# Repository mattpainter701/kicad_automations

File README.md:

<p align="center">

</p>

<p align="center">
  <strong>Programmatic KiCad schematic generation, strict validation, and manufacturing export<br>
  designed for AI-assisted hardware workflows — Claude Code, Codex, and offline CLI.</strong>
</p>

---

## How It Works

Every path through Circuit Weaver follows the same contract: **describe the design → validate → generate KiCad artifacts**. The diagram above shows what each module does and which function it calls. Pick your entry point (Claude Code skill, Codex agent, or CLI wizard) and the rest is automatic.

---

<!-- capability-registry:start -->
## Capability Contract

This table is generated from the checked-in capability registry. Regenerate it with `python scripts/gen_capability_docs.py`; do not edit it by hand.

Verification is conservative: a capability only claims the evidence level its public path actually verifies. **not applicable** means an operational capability makes no design-artifact verification claim; it is not a lower verification level.

| CLI capability | Maturity | Public surfaces | Verification contract | Evidence | Since |
|---|---|---|---|---|---|
| `validate` | beta | CLI: `validate`; Python: `circuit_weaver.dispatcher:validate_design`; HTTP: `POST /validate; POST /mvp/validate`; MCP: `validate_design`; Skill: `circuit-weaver` | `static-parse` → `static-parse` | `command-contract`, `static-parse` | 0.32.1 |
| `apply-patch` | beta | CLI: `apply-patch`; Python: `circuit_weaver.dispatcher:apply_design_patch`; HTTP: `POST /mvp/apply-patch` | `static-parse` → `static-parse` | `command-contract`, `static-parse` | 0.32.1 |
| `generate` | experimental | CLI: `generate`; Python: `circuit_weaver.dispatcher:generate_artifacts`; HTTP: `POST /generate; POST /mvp/generate`; MCP: `generate_artifacts`; Skill: `circuit-weaver` | `static-parse` → `static-parse` | `command-contract`, `static-parse`, `kicad-load`, `erc` | 0.32.1 |
| `review-report` | experimental | CLI: `review-report`; Skill: `circuit-weaver` | `static-parse` → `static-parse` | `command-contract`, `static-parse` | 0.32.1 |
| `diff` | beta | CLI: `diff`; Python: `circuit_weaver.dispatcher:diff_designs`; HTTP: `POST /mvp/diff` | `static-parse` → `static-parse` | `command-contract`, `static-parse` | 0.32.1 |
| `ingest-pcb-feedback` | beta | CLI: `ingest-pcb-feedback`; Python: `circuit_weaver.dispatcher:ingest_pcb_feedback`; HTTP: `POST /mvp/pcb-feedback` | `static-parse` → `static-parse` | `command-contract`, `static-parse` | 0.32.1 |
| `import-placement` | review_only | CLI: `import-placement`; Skill: `circuit-weaver` | `static-parse` → `static-parse` | `command-contract`, `static-parse` | 0.32.1 |
| `list-templates` | beta | CLI: `list-templates`; HTTP: `GET /templates` | not applicable (operational) | `command-contract` | 0.32.1 |
| `scaffold` | beta | CLI: `scaffold`; Skill: `circuit-weaver` | `static-parse` → `static-parse` | `command-contract`, `static-parse` | 0.32.1 |
| `register-ic` | experimental | CLI: `register-ic` | `static-parse` → `static-parse` | `command-contract`, `static-parse` | 0.32.1 |
| `resolve-symbol` | experimental | CLI: `resolve-symbol` | not applicable (operational) | `command-contract` | 0.33.0 |
| `export-jlcpcb` | review_only | CLI: `export-jlcpcb`; Skill: `circuit-weaver` | `static-parse` → `static-parse` | `command-contract`, `static-parse` | 0.32.1 |
| `export-gerbers` | review_only | CLI: `export-gerbers`; Skill: `circuit-weaver` | `static-parse` → `static-parse` | `command-contract`, `static-parse` | 0.32.1 |
| `cost-bom` | experimental | CLI: `cost-bom`; Skill: `circuit-weaver` | `static-parse` → `static-parse` | `command-contract`, `static-parse` | 0.32.1 |
| `import-design` | experimental | CLI: `import-design`; Python: `circuit_weaver.design_import:import_design`; Skill: `circuit-weaver` | `static-parse` → `static-parse` | `command-contract`, `static-parse` | 0.32.1 |
| `analyze-design` | experimental | CLI: `analyze-design`; Python: `circuit_weaver.design_import:analyze_design`; Skill: `circuit-weaver` | `static-parse` → `static-parse` | `command-contract`, `static-parse` | 0.32.1 |
| `status` | beta | CLI: `status`; Python: `circuit_weaver.project_state:get_project_state_summary`; Skill: `circuit-weaver` | not applicable (operational) | `command-contract` | 0.32.1 |
| `resume` | experimental | CLI: `resume`; Python: `circuit_weaver.project_state:resume_project`; Skill: `circuit-weaver` | not applicable (operational) | `command-contract` | 0.32.1 |
| `design-wizard` | experimental | CLI: `design-wizard`; Skill: `design-wizard` | `static-parse` → `static-parse` | `command-contract`, `static-parse` | 0.32.1 |
| `place-pcb` | experimental | CLI: `place-pcb`; Skill: `circuit-weaver` | `static-parse` → `static-parse` | `command-contract`, `external-tool`, `user-supplied` | 0.32.1 |
| `log-status` | beta | CLI: `log-status` | not applicable (operational) | `command-contract` | 0.32.1 |
| `log-view` | beta | CLI: `log-view` | not applicable (operational) | `command-contract` | 0.32.1 |
| `autoroute` | review_only | CLI: `autoroute`; Skill: `circuit-weaver` | `static-parse` → `static-parse` | `command-contract`, `external-tool`, `user-supplied` | 0.32.1 |
| `install-skills` | experimental | CLI: `install-skills` | not applicable (operational) | `command-contract` | 0.32.1 |
| `schema` | beta | CLI: `schema` | not applicable (operational) | `command-contract` | 0.32.1 |
| `harvest-specs` | experimental | CLI: `harvest-specs` | `static-parse` → `static-parse` | `command-contract`, `external-tool` | 0.32.1 |
| `extract-specs` | experimental | CLI: `extract-specs` | `static-parse` → `static-parse` | `command-contract`, `user-supplied` | 0.32.1 |
| `fetch-spice` | experimental | CLI: `fetch-spice` | `static-parse` → `static-parse` | `command-contract`, `external-tool` | 0.32.1 |
| `cache` | beta | CLI: `cache` | not applicable (operational) | `command-contract` | 0.32.1 |
| `cache stats` | beta | CLI: `cache stats` | not applicable (operational) | `command-contract` | 0.32.1 |
| `cache clear` | review_only | CLI: `cache clear` | not applicable (operational) | `command-contract` | 0.32.1 |
| `optimize-placement` | review_only | CLI: `optimize-placement`; Skill: `circuit-weaver` | `static-parse` → `static-parse` | `command-contract`, `static-parse` | 0.32.1 |
| `placement-viewer` | review_only | CLI: `placement-viewer`; Skill: `circuit-weaver` | `static-parse` → `static-parse` | `command-contract`, `static-parse` | 0.32.1 |
| `si-constraints` | experimental | CLI: `si-constraints` | `static-parse` → `static-parse` | `command-contract`, `static-parse` | 0.32.1 |
| `thermal-analysis` | experimental | CLI: `thermal-analysis` | `static-parse` → `static-parse` | `command-contract`, `static-parse` | 0.32.1 |
| `export-dual-cpl` | review_only | CLI: `export-dual-cpl` | `static-parse` → `static-parse` | `command-contract`, `static-parse` | 0.32.1 |
| `panelize` | experimental | CLI: `panelize` | `static-parse` → `static-parse` | `command-contract`, `static-parse` | 0.32.1 |
| `design-enclosure` | experimental | CLI: `design-enclosure` | `static-parse` → `static-parse` | `command-contract`, `static-parse` | 0.32.1 |
| `check-dfm` | review_only | CLI: `check-dfm` | `static-parse` → `static-parse` | `command-contract`, `static-parse` | 0.32.1 |
| `generate-docs` | experimental | CLI: `generate-docs` | `static-parse` → `static-parse` | `command-contract`, `static-parse` | 0.32.1 |
| `erc` | review_only | CLI: `erc` | `kicad-load` → `erc` | `command-contract`, `kicad-load`, `erc` | 0.32.1 |
| `doctor` | beta | CLI: `doctor` | not applicable (operational) | `command-contract` | 0.32.1 |
| `repair` | experimental | CLI: `repair`; Python: `circuit_weaver.repair_service:apply_no_connect` | `static-parse` → `static-parse` | `command-contract`, `static-parse` | 0.35.0 |
| `confidence` | review_only | CLI: `confidence`; Skill: `circuit-weaver` | `static-parse` → `static-parse` | `command-contract`, `static-parse` | 0.32.1 |
| `manufacturing-readiness` | beta | CLI: `manufacturing-readiness`; Python: `circuit_weaver.manufacturing_readiness:read_manufacturing_readiness`; HTTP: `POST /manufacturing-readiness`; MCP: `manufacturing_readiness`; Skill: `circuit-weaver` | `static-parse` → `static-parse` | `command-contract`, `fabrication-ready` | 0.34.0 |
| `simulate` | experimental | CLI: `simulate`; Skill: `circuit-weaver` | `static-parse` → `static-parse` | `command-contract`, `static-parse` | 0.32.1 |
| `discover` | beta | CLI: `discover`; MCP: `discover_projects`; Skill: `circuit-weaver` | not applicable (operational) | `command-contract` | 0.32.1 |
| `save-research` | experimental | CLI: `save-research`; Skill: `circuit-weaver` | `static-parse` → `static-parse` | `command-contract`, `static-parse` | 0.32.1 |
| `log-event` | beta | CLI: `log-event` | not applicable (operational) | `command-contract` | 0.32.1 |
<!-- capability-registry:end -->

## Quick Start

**Step 1 — Install**

```bash
pip install circuit-weaver
```

**Step 2 — Register the skill** *(one-time, for Claude Code / Codex / OpenCode)*

```bash
circuit-weaver install-skills            # install for all supported agent platforms
circuit-weaver install-skills --dry-run  # preview without touching disk
circuit-weaver install-skills --force --backup   # resolve conflicts, back up every replaced file
```

> **Upgrade safety:** each installed skill has a provenance manifest containing hashes for every
> managed file. A pristine older release upgrades automatically. A file changed or deleted by the
> user is preserved and reported as a conflict, and the command exits non-zero. Pass `--force`
> only after reviewing conflicts; add `--backup` to preserve every replaced file.

**Step 3 — Launch**

```text
# Claude Code:
/circuit-weaver

# Codex:
$circuit-weaver

# OpenCode: ask it to use circuit-weaver (loaded through its skill tool).

# Or run offline without any agent:
circuit-weaver design-wizard
```

The skill walks through IC selection, spec validation, schematic generation, and the electrical-PCB handoff.

---

## Research Traceability

Agentic research runs are expected to persist their output into `output/research/`.
That directory is the source of truth for why an IC was chosen, which citations
backed it, and which backend produced the result.

For Codex / Claude / OpenCode workflows, Step 2 IC research should stay in the
current agent session. If a premium-research command would delegate to a
subagent or fails with a model/tool conflict, use the platform's native web
tools instead and persist the backend that actually ran.

```bash
# Check which backend and depth are active before research starts
circuit-weaver doctor

# Optional: force backend/depth selection for agent workflows
export CIRCUIT_WEAVER_RESEARCH_BACKEND=standard   # or sonar-pro / auto
export CIRCUIT_WEAVER_RESEARCH_DEPTH=fast         # or normal
# PowerShell: $env:CIRCUIT_WEAVER_RESEARCH_BACKEND="standard"
# PowerShell: $env:CIRCUIT_WEAVER_RESEARCH_DEPTH="fast"

# Persist a completed research result
circuit-weaver save-research --project-dir ./output --file research.json
```

Each saved run produces `{slug}.json`, `{slug}.md`, and `summary.md`, and the
matching `design.log` entry records the canonical JSON path for later audit.

---

## Branch Maintenance

Use `scripts/cleanup_branches.py` to audit stale local branches before pruning them.
The command is dry-run by default and only targets merged, unprotected branches,
so dated work can be reviewed without risking useful code. When run with
`--delete`, deleted branch tips are archived under `refs/archive/branches/<name>`
unless `--no-archive` is explicitly supplied.

```bash
python scripts/cleanup_branches.py                 # audit only
python scripts/cleanup_branches.py --delete        # prune merged stale branches and keep archives
python scripts/cleanup_branches.py --force-unmerged # include unmerged branches only when intentionally forced
```

---

## What You Get

A successful default `generate` run produces a complete artifact bundle
(`--no-placement-review` deliberately omits the four placement-review files):

| Artifact | File | Description |
|-|-|-|
| KiCad schematic hierarchy | `{project}.kicad_sch` plus functional sub-sheets | Real, loadable hierarchy; explicit block `section` values remain separate professional sheets and support passives follow their owner |
| Markdown design report | `{project}_report.md` | Validation results, component summary, and design notes |
| Placement review | `placement_result.json`, `placement_review_context.json`, `placement.svg`, `placement_editor.html` | Exhaustive, reference-reconciled heuristic proposal with review blockers and official-reference context; never fabrication data |
| Assembly inventory | `assembly_manifest.json` | Stable physical-part references, including generated support passives |
| Evidence ledger | `evidence_manifest.json` | Stable component, pinout, footprint, parameter, finding, tool, and verification provenance IDs |
| Canonical spec and IR | `canonical_spec.yaml`, `design_ir.json` | Normalized source of truth and generated design IR |
| Validation evidence | `validation_report.json`, `placement_readiness.json` | Machine-readable release/readiness checks |
| Artifact inventory | `artifact_manifest.json` | Portable relative paths, verification state, kinds, and sizes for every generated artifact |
| Test point map | `{project}_test_points.csv` | Auto-detected power, clock, bus, and differential-pair nets |
| Firmware stubs (when applicable) | `{project}_pinout.csv`, `.ioc`, `sdkconfig.defaults` | MCU pin map and STM32/ESP32 co-design files |

---

## Resume or Analyze an Existing Design

Circuit Weaver keeps restartable state in `<project>/.circuit-weaver/project.json`.
Import is non-destructive: source KiCad, PCB, Gerber, drill, and ZIP files are
inventoried and hashed rather than regenerated.

```bash
# Import a KiCad project, a single KiCad file, a Gerber directory, or a ZIP
circuit-weaver import-design ./existing_board --analyze

# Inspect durable state or get a deterministic restart plan
circuit-weaver status ./existing_board
circuit-weaver resume ./existing_board

# Re-run every applicable bundled analyzer; unchanged results are cached
circuit-weaver analyze-design ./existing_board
```

Use `--project-dir <dir>` when state should live somewhere other than the
source directory. Use `--force` only to intentionally replace a changed import
source set, ZIP staging tree, or cached analysis. Netlist-only imports are
inventoried, but analysis is reported as unsupported because a netlist alone
does not contain schematic or physical-layout evidence.

### Bounded no-connect repair

The first experimental imported-design repair is deliberately narrow: it can
add one explicit KiCad no-connect marker only when a
`circuit-weaver-repair-metadata/v1` envelope binds the exact source hash,
analyzer component/pin identity, a v2 finding, and its validated evidence
manifest. Build that envelope with
`circuit_weaver.repair_service.build_no_connect_metadata`; the matching trusted
finding producer is `no_connect_finding_from_intent`. Both require current,
verified user evidence whose exact `pin:REF.NUMBER` claim says the pin is
intentionally unused. Raw analyzer JSON or an unbound boolean is rejected.

The service then independently proves the component UUID/library ID, pin
coordinate, and absence of a net, wire, label, junction, bus entry,
hierarchical sheet pin, power symbol, or coincident component pin. The plan is
reviewable JSON; the apply step will not infer approval from that file.

```bash
circuit-weaver repair suggest board.kicad_sch repair-metadata.json \
  --ref U1 --pin 4 \
  --finding-id FND-0123456789ab \
  --evidence-id EV-VALIDATION-0123456789ab \
  --output no-connect-plan.json

# Review the plan and copy its plan_sha256 through the approval channel.
circuit-weaver repair apply no-connect-plan.json repair-metadata.json \
  --approved-plan-hash <approved-plan-sha256> \
  --reviewer <reviewer> \
  --finding-id FND-0123456789ab \
  --evidence-id EV-VALIDATION-0123456789ab

circuit-weaver repair verify board.kicad_sch no-connect-plan.json
```

The public capability guarantee is static parsing. Run KiCad ERC after review;
unsupported topology, geometry, part replacement, and pin-remapping repairs
fail closed instead of being improvised. Apply holds cross-process source and
audit locks, keeps an exact hard-linked preimage through publication, and uses
prepared/committed append-only audit events so an interrupted successful
publication can be recovered on retry. Lock hardlinks and reparse aliases are
rejected before mutation; the default audit sidecar cannot escape through a
directory junction. On Windows, atomic replacement preserves and verifies the
target owner, group, and DACL access semantics. Applications that write
schematics without honoring Circuit Weaver's lock remain outside the
cooperative locking contract; snapshot, identity, and post-image checks still
detect ordinary write races and preserve observed user bytes rather than
rolling over them.

---

## PCB Placement Workflow

Circuit Weaver generates a review-only placement proposal, then KiCad creates
the electrical PCB. The SVG/HTML/JSON proposal is never a PCB, CPL, or other
fabrication artifact.

### 1 — Generate initial placement

`generate` returns the path to `artifact_manifest.json`. Resolve that manifest's portable `root_schematic` and artifact paths relative to the manifest directory instead of guessing filenames. Check `verification_status` before claiming KiCad verification. Placement review is enabled by default:

```bash
circuit-weaver generate design.yaml -o ./output
# → output/{project}.kicad_sch
# → output/placement_result.json
# → output/placement_review_context.json
# → output/placement.svg
# → output/placement_editor.html
# → output/{project}_report.md
```

`placement_result.json` must contain the exact `assembly_manifest.json`
reference inventory. It remains `fabrication_ready: false` by design. Review
its overlap, boundary, support-part, geometry, sourcing, and constraint
blockers. `placement_review_context.json` records constraints, targeted
research prompts, and official component/reference-layout links available to
the agent; manufacturer documentation remains authoritative.

### 2 — Optimize with simulated annealing

```bash
# Basic optimization (5 000 iterations, reproducible with seed)
circuit-weaver optimize-placement design.yaml --iterations 5000 --seed 42 \
    -o output/placement.json

# Thermal-aware strategy (minimizes hotspot proximity)
circuit-weaver optimize-placement design.yaml --strategy thermal --iterations 10000 \
    -o output/placement.json

# Read component thermal/SI specs from YAML files
circuit-weaver optimize-placement design.yaml --specs-dir ./specs/
```

The optimizer minimizes: overlap, boundary violations, thermal clustering, and DFM zone penalties via simulated annealing. Returns a placement JSON with x/y/rotation/layer per component.

### 3 — Review in the interactive viewer

Open the generated `output/placement_editor.html`, or generate a standalone
viewer for a different optimizer configuration:

```bash
circuit-weaver placement-viewer design.yaml -o output/viewer.html
```

Opens a self-contained HTML file with:
- Click-to-highlight nets
- Component hover tooltips (value, footprint, MPN)
- Thermal heatmap overlay (blue → red gradient by power dissipation)
- CSV export button for placement data

### 4 — Create the electrical PCB in KiCad

Open `artifact_manifest.json`, then open its `root_schematic`, assign and verify footprints, and run **Update PCB from Schematic**. Save that electrically annotated board under a separate name. Only this board has the pads and nets required by routing, DFM, and Gerber export.

Apply reviewed SVG coordinates only to that real electrical PCB. The default
import is strict: every PCB reference must appear exactly once in the SVG, and
unexpected or missing references block the write.

```bash
circuit-weaver import-placement output/placement.svg board.kicad_pcb \
    -o board_placed.kicad_pcb --dry-run
circuit-weaver import-placement output/placement.svg board.kicad_pcb \
    -o board_placed.kicad_pcb

# Intentional subset update only; unknown SVG references still fail.
circuit-weaver import-placement subset.svg board.kicad_pcb \
    -o board_placed.kicad_pcb --allow-partial
```

### 5 — Place and route the real board

After forward annotation, add a rectangular Edge.Cuts outline and lock connectors
that must remain fixed. Place the actual library footprints, route, import the
tracks, and check the final PCB:

```bash
circuit-weaver place-pcb board.kicad_pcb -o board_placed.kicad_pcb --seed 7
circuit-weaver autoroute board_placed.kicad_pcb --attempts 3 \
    --routed-board board_routed.kicad_pcb
```

KiCad's native Python is discovered separately from your application Python.
Freerouting and a compatible Java runtime are required for routing. The input
board must have real pads and nets; padless previews are rejected. Placement
currently requires an unrouted rectangular board without zones. It preserves
locked footprints and board sides, uses real courtyards and rotated pad locations,
and checks physical DRC. Routing publishes the final board only after KiCad DRC
passes, preserving project rules. See [setup and limits](docs/routing-placement-search.md).

### 6 — DFM check and panelization

```bash
# Check clearances, pad sizes, and DFM rules
circuit-weaver check-dfm electrical_board.kicad_pcb --profile jlcpcb

# Get panel layout suggestions for small boards
circuit-weaver panelize --board-width 50 --board-height 40 --qty 100

# Export dual-sided CPL (top + bottom)
circuit-weaver export-dual-cpl design.yaml --pcb electrical_board.kicad_pcb -o ./jlcpcb

# Export a reconciled JLCPCB delivery and inspect its commit manifest
circuit-weaver export-jlcpcb design.yaml --pcb electrical_board.kicad_pcb -o ./jlcpcb
# → bom_jlcpcb.csv, cpl_jlcpcb.csv, README_jlcpcb.txt, delivery_manifest.json
```

Without `--pcb`, `export-jlcpcb` is intentionally BOM-only. A supplied board
must match every assembly reference and footprint before CPL publication.
Treat `delivery_manifest.json` as the delivery status/commit marker.

---

## CLI Reference

```bash
# ── Design lifecycle ──────────────────────────────────────────────────────────
circuit-weaver validate design.yaml               # Validate spec (no files written)
circuit-weaver generate design.yaml -o ./output  # Full artifact bundle
circuit-weaver erc output/{project}.kicad_sch      # Use root_schematic from artifact_manifest.json
circuit-weaver diff old.yaml new.yaml             # Semantic diff + optional SVG
circuit-weaver import-design ./legacy_board --analyze
circuit-weaver status ./legacy_board
circuit-weaver resume ./legacy_board
circuit-weaver analyze-design ./legacy_board

# ── Placement ─────────────────────────────────────────────────────────────────
circuit-weaver optimize-placement design.yaml --iterations 5000 --seed 42 -o output/placement.json
circuit-weaver placement-viewer design.yaml -o output/viewer.html
circuit-weaver import-placement placement.svg board.kicad_pcb -o out.kicad_pcb
circuit-weaver import-placement subset.svg board.kicad_pcb -o out.kicad_pcb --allow-partial
circuit-weaver check-dfm electrical_board.kicad_pcb --profile jlcpcb
circuit-weaver panelize --board-width 50 --board-height 40 --qty 100
circuit-weaver export-dual-cpl design.yaml --pcb electrical_board.kicad_pcb -o ./jlcpcb

# ── Simulation & confidence ──────────────────────────────────────────────────
circuit-weaver simulate design.yaml -o ./sims      # Run SPICE simulations (ngspice)
circuit-weaver confidence design.yaml --run-sims   # Full design readiness score (0-100)
circuit-weaver confidence design.yaml -o report.html --pcb board.kicad_pcb

# ── BOM and manufacturing ─────────────────────────────────────────────────────
circuit-weaver cost-bom design.yaml --qty 1,10,100
circuit-weaver export-jlcpcb design.yaml --pcb electrical_board.kicad_pcb -o ./jlcpcb
circuit-weaver export-gerbers electrical_board.kicad_pcb -o ./gerbers

# ── Project management ───────────────────────────────────────────────────────
circuit-weaver discover                             # Auto-detect projects in CWD
circuit-weaver discover --json --depth 2            # JSON output, search 2 levels deep
circuit-weaver save-research --project-dir ./output --file research.json
circuit-weaver log-event ./project --type scoring --message "Review done"
circuit-weaver doctor                               # Check credentials, backends, and tool availability

# ── Design tools ──────────────────────────────────────────────────────────────
circuit-weaver scaffold --template buck --ref U1   # New spec from template
circuit-weaver list-templates --verbose             # Browse 37 subcircuit templates
circuit-weaver design-enclosure --board-width 50 --board-height 40 -o enclosure.scad
circuit-weaver harvest-specs design.yaml           # Download datasheets + extract specs
circuit-weaver fetch-spice design.yaml             # Fetch SPICE models (TI, ADI, Microchip…)
```

Run `circuit-weaver --help` or `circuit-weaver <subcommand> --help` for full flag reference.

---

## Python API

```python
from circuit_weaver.dispatcher import (
    validate_design,
    apply_design_patch,
    generate_artifacts,
    diff_designs,
    ingest_pcb_feedback,
)
from circuit_weaver.design_import import analyze_design, import_design
from circuit_weaver.project_state import get_project_state_summary, resume_project

# Validate a canonical design spec
report = validate_design(spec)

# Apply a transactional patch and re-validate
result = apply_design_patch(spec, patch)

# Generate the full bundle; require real KiCad for a release-quality claim
bundle = generate_artifacts(spec, output_dir="out/design", require_kicad=True)

# Non-destructively open and analyze KiCad/PCB/Gerber/ZIP sources
opened = import_design("legacy-board.zip", project_dir="work/legacy", analyze=True)
state = get_project_state_summary(opened["project_root"])
restart_plan = resume_project(opened["project_root"])
analysis = analyze_design(opened["project_root"])

# Semantic diff between two specs
changes = diff_designs(old_spec, new_spec)

# Feed PCB layout feedback back into the design spec
updated = ingest_pcb_feedback(spec, pcb_feedback)
```

### Validation groups

`validate_design` runs five grouped checks and returns a structured `ValidationReport`:

| Group | What it checks |
|-|-|
| `structural` | Topology, block connections, hierarchy integrity |
| `electrical` | Power rails, ground nets, net continuity |
| `implementation` | Part bindings, footprint assignments, pinout verification |
| `placement_readiness` | **Hard-gated** — dangling buses, missing I2C pull-ups, orphan interfaces, floating enables; never bypassable by `--no-require-valid` |
| `presentation` | Labels, pin numbers, sheet readability |

### HTTP API

```bash
uvicorn circuit_weaver.api:app --host 0.0.0.0 --port 5000
```

| Endpoint | Method | Description |
|-|-|-|
| `/health` | GET | Service health |
| `/capabilities` | GET | Machine-readable capability maturity and verification contract |
| `/templates` | GET | Available subcircuit templates |
| `/generate` | POST | YAML spec → ZIP of `.kicad_sch` + report |
| `/validate` | POST | YAML spec → validation JSON |
| `/mvp/apply-patch` | POST | Transactional patch + re-validation |
| `/mvp/diff` | POST | Semantic diff between two specs |
| `/mvp/pcb-feedback` | POST | Merge PCB layout feedback into spec |
| `/mvp/generate` | POST | JSON/YAML spec to a ZIP with a portable artifact manifest |

---

## What's New in v0.33.0

Circuit Weaver `v0.33.0` makes electrical recommendations measurable and traceable instead of relying on silent universal defaults.

| Area | Improvement |
|-|-|
| Evidence-backed passives | Shared versioned equations, explicit datasheet/equation/bounded-fallback precedence, declared E-series policy, and retained `CALC-*` evidence for critical support networks. |
| Fail-closed synthesis | Invalid or unsupported regulator, crystal, reset, USB-C, CAN/RS-485, and analog support values are withheld under `CW-PSV-*` findings before emission. |
| Typed power accuracy | Rail limits, direction, current envelopes, sequencing, tolerance, and provenance flow through ingest, validation, reports, placement context, and repair. |
| Identity safety | Exact MPN/package, symbol pin, footprint pad, and two-source reconciliation block physical CPL handoff when identity or pin-to-pad coverage is ambiguous. |
| Calibrated validation | Severity is separate from detection confidence; actionable findings name the constraint, observation, evidence, and safest next action. |
| Published scorecard | A 40-fixture benchmark covers 33 emitted/contract rule IDs—14 scored and 19 explicitly unsupported—with supported precision/recall at 1.000/1.000. |

<details><summary>v0.32.0</summary>

Circuit Weaver `v0.32.0` is an integrity and compatibility release for agent workflows and programmatic users.

| Area | Improvement |
|-|-|
| Schematic integrity | Deterministic sheet/reference allocation, collision-safe symbol naming, strict rendered pin maps, final S-expression checks, and safer label/wire movement for dense designs. |
| Truthful verification | ERC runs against the exact final schematic; results expose `kicad_verified` and `verification_status`, while `--require-kicad` fails closed when verification cannot run. |
| Durable workflows | Atomic status/resume state plus non-destructive KiCad, PCB, Gerber/drill, and ZIP import with fingerprinted cached analysis. |
| Professional hierarchy | Explicit block sections remain separate functional sheets, support parts retain ownership, and filenames are collision-safe. |
| Placement review | Exhaustive assembly reconciliation, blocker-aware JSON/context, official-reference links, and editable SVG/HTML; review artifacts are never fabrication data. |
| Manufacturing and routing | JLC/CPL export reconciles real PCB references and footprints; Freerouting publishes validated SES sessions and reports incomplete routing as partial. |
| Agent workflows | Portable kebab-case skills, narrower triggers, provenance-aware upgrades, and aligned Codex, Claude, and OpenCode installation paths. |
| Programmatic compatibility | Restored legacy imports and deprecated aliases, strict YAML parsing, exhaustive artifact inventory, and real placement SVG data. |
| Release reliability | Python 3.10-3.14, blocking Windows coverage, exact-wheel tests, live MCP tests, and KiCad 8/9/10 generation and ERC gates before PyPI publication. |

</details>

<details><summary>v0.31.0</summary>

Circuit Weaver `v0.31.0` collected the Sprint 53-54 schematic layout quality work and graduated the prior `0.30.x` sprint-release series into a minor release.

| Sprint | Feature |
|-|-|
| 54 | **Layout quality zero-crossing gate** — all quality-gated sample schematics now target zero wire-through-body crossings, with body-aware stubs, tapped-rail splitting, unrounded keep-outs, and generator-visible layout-quality warnings/reports. |
| 54 | **Density, sheet splitting, and autorouter hardening** — connector-heavy layouts now use a continuous density score, oversized sheets split instead of cramming onto A0, and Freerouting preflight/effort/timeout handling fail closed with clearer remediation. |
| 53 | **Schematic readability and passive placement** — sidecar passives, passive motifs, and local wiring now use occupancy-aware placement and body-aware routing to remove symbol overlaps and sharply reduce wire-body crossings. |
| 52 | **Part-neutral repair and schema plumbing** — normalized `pin_roles` now flow through `ComponentDef`, `ic_data`, EasyEDA imports, generic-builder outputs, and cache round-trips, so SPI/UART repair can operate from shared capabilities instead of exact MPN branches. |
| 52 | **Generation and placement hardening** — readiness gating now lives in `generate_from_components`, generic bypass policy is centralized, orphan non-power nets are hard-gated in placement-readiness, and PCB placement preview now penalizes long connected pairs instead of staying purely zone-based. |
| 51 | **Restart and validation flows are more truthful** — `log-status` works for validate-only sessions, persisted validation summaries now reflect the final verdict, Windows text-mode validation falls back to ASCII, and bad data-driven `ic` resolution now fails closed instead of silently substituting another part. |
| 51 | **Workflow skills are less brittle under long-running sessions** — `/circuit-weaver` now reports the installed CLI version first, long steps require timeout follow-up checks, and the validate-output recipe now preserves JSON on stdout instead of mixing it with stderr. |
| 50 | **Generic builder parity gate is closed** — the data-driven path now covers the remaining sensor-front-end, shared-bus, battery, display, and passive-diode contracts that were blocking the sample/corpus release gate; the full suite passes `1009 passed, 1 skipped`. |
| 50 | **CLI/package workflows are hardened for PyPI use** — read-only spec directories no longer crash file logging, unreadable `~/.config/secrets.env` no longer breaks `doctor` or unknown-part fallback, and the bundled skill payload is resynced byte-identical with `skills/`. |
| 49 | **Wizard intake now tiers by experience level** — the offline `design-wizard` asks for experience before requirements, uses compact design-brief intake for advanced/professional users, and no longer forces the same opening question flow on every user. |
| 49 | **Specialized RF workflows are now framed correctly** — Circuit Weaver skills now route radar / RF / microwave requests into a research-first custom engineering flow instead of treating the lack of turnkey coverage as an out-of-scope rejection. |
| 45-47 | **Schematic paper over-promotion fix** — `layout_sheet()` now starts from the allocator-selected paper size and only promotes if it doesn't fit. Small IoT-sensor-class designs no longer cascade to A2. Tighter title-block clearance keeps content on A3. |
| 45-47 | **Design log severity mapping** — `DesignLogHandler` maps Python `WARNING` records to `"warning"` type instead of `"error"` in `design.log`. |
| 45-47 | **BME688 bundled IC data** — sensor pin/footprint metadata shipped in `ic_data/misc.json`. `IoT_AQ_Sensor_v2` resolves without local `custom.json`. |
| 45-47 | **JLCPCB assembly variants** — `generate_assembly_variants()` supports `include_refs`, `exclude_refs`, `dnp_refs` subsets; per-variant BOM/CPL output. |
| 45-47 | **Allocator + placement-readiness tests** — 52 new dedicated tests closing Sprint 42 coverage gaps. |
| 44 | **Label collision avoidance** — overlapping labels on dense sheets are detected and shifted along wire-stub direction. Same-name labels skipped. |
| 44 | **Validate-all regression gate** — 14+1 sample YAMLs now validate clean; CI gate enforces zero hard errors. |
| 44 | **Sourcing auditor alternates** — queries LCSC/DigiKey for functionally similar parts when a component has CRITICAL/WARNING risk. |
| 44 | **MCP server** — `circuit-weaver-mcp` entry point for AI agent tool access via FastMCP. |
| 44 | **Wire-crossing minimization** — placer penalizes crossing-dense placements; bus signal groups detected for future parallel routing. |
| 43 | **Density-scaled grid spacing** — inter-component gaps scale to spread content across available page area, preventing corner-clustering on large sheets. |
| 43 | **Annotation overlap prevention** — per-IC annotations shift down when they would collide, with overflow line drops. |
| 43 | **Lane routing counter recycling** — capped at 6 with modulo wrap, preventing lanes from drifting 194mm from the IC. |

</details>

<details><summary>v0.27.0</summary>

| Sprint | Feature |
|-|-|
| 40 | **Cache-rebuilt components no longer ship as silent 2-pin stubs** — `SymbolResolver._rebuild_from_cache` now marks cache hits without real pin topology as `pinout_source="stub"`, so the existing `pinout-source` validator gate catches any multi-pin IC (sensor, MCU, H-bridge, gate driver, regulator) that would otherwise emit as a passive. The EasyEDA tier now persists full pin + power + bypass / strap topology via `symbol_cache.component_def_to_cache_payload()` so round-tripping a part through the cache preserves everything |
| 40 | **Schematic emission invariant** — `primitives.assemble_sheet` now dedupes structural duplicates before writing (symbol instances, wires, global / hierarchical labels, no-connects, junctions, UUIDs). Catches the placer / topology-dispatcher double-emission class of bug that was causing stacked passives, duplicate wires, and shared-UUID power symbols |
| 40 | **Placement PCB preview never fabricates footprints or synthetic pads** — the generator field now reads `placement_preview` so reviewers can tell the file apart from fab-ready output; missing footprint bindings emit `Placement_Preview:Missing_<ref>` placeholders instead of the old SOIC-8 fallback; and no synthetic pads are emitted for any component. KiCad's schematic → PCB forward annotation is the authoritative source of pads |
| 40 | **`generate` enforcement is now deterministic across runs** — structural + implementation category errors always raise, regardless of `require_valid`. `--no-require-valid` now only bypasses soft electrical warnings (dangling dev signals, crystal load-cap tolerance) and the bypass is logged at WARNING level. Two runs on the same spec + cache state always reach the same verdict |
| 40 | **Report-fidelity diagnostic** — `report.verify_report_fidelity(report_text, components)` flags references to component refs, net names, or annotations that don't exist in the resolved design. Catches the ghost-feature pattern where a report claimed "BME688 I2C + pull-ups" or "LED + current-limit R4" without any backing wires |
| 40 | **Five-archetype generation regression corpus** — `tests/test_generation_corpus.py` runs `generate_artifacts` end-to-end on LED driver, IoT sensor, motor controller, USB bridge, and FPGA power carrier samples, enforcing all three Sprint 40 invariants. Breadth-guard test keeps the corpus at ≥ 5 archetypes |
| 39 | **Step 2 IC research stays in the current agent session** across Codex / Claude / OpenCode instead of delegating to a spawned `/research` / `research-analyst` path that could trigger model conflicts; workflow docs and skill prompts now describe the real behavior |
| 39 | **Research-depth latency selector** — `design-wizard --research-depth {fast,normal}` persists into spec metadata; `doctor` reports the effective depth; Circuit Weaver skill uses a smaller query budget in `fast` mode |

</details>

<details><summary>v0.26.1</summary>

| Sprint | Feature |
|-|-|
| 38 | **Research workflow is now reproducible end-to-end** — `design-wizard --research-backend` persists the effective backend into spec metadata, `save-research` records the canonical JSON artifact path in `design.log`, and the workflow docs now tell agents to treat `output/research/` as the source of truth |
| 38 | **Resolver credential diagnostics now match real runtime behavior** — DigiKey checks both `DIGIKEY_CLIENT_ID` and `DIGIKEY_CLIENT_SECRET`, Mouser honors `MOUSER_SEARCH_API_KEY` through the shared credential loader, and `circuit-weaver doctor` now reports both credential states directly |
| 37 | **Research persistence + backend selection shipped in the CLI** — `circuit-weaver save-research`, `CIRCUIT_WEAVER_RESEARCH_BACKEND`, and `circuit-weaver doctor` backend reporting are now available in the published package |

</details>

<details><summary>v0.25.0</summary>

| Sprint | Feature |
|-|-|
| 35 | **`install-skills` collision protection** — stopped silently overwriting a curated `SKILL.md`; added `--force`, `--backup`, and `--dry-run` with collision reporting for review |
| 35 | **All 11 skills bundled in the wheel** — the full set, including `design-wizard`, is kept in sync by `scripts/sync_bundled_skills.py` with CI and pre-commit drift guards |
| 35 | **Windows CI leg** — `windows-latest` / Python 3.12 smoke run (non-blocking first sprint) covering CLI commands, doctor, skill installer, and `python -m circuit_weaver --version` |

</details>

<details><summary>v0.24.0</summary>

| Sprint | Feature |
|-|-|
| 34 | **Data-Driven Template Engine** — IC data now lives in JSON files under `src/circuit_weaver/ic_data/` (11 categories). New `topology_builders.py` produces schematic fragments dynamically, replacing hardcoded template classes |
| 34 | **7 New Subcircuit Templates** — RTC (DS3231, PCF8563), EEPROM (24LCxx, 25LCxx), wireless modules (nRF52, ESP32, LoRa), USB-C connectors, SPI bus conditioning, voltage references (REF5025, LM4040), generic connectors — total template count now 37 |
| 34 | **IC Registration CLI** — `scripts/extract_ic_data.py` harvests IC entries from datasheet research; `register_ic()` API persists to `custom.json` |
| 33 | **Platform Compatibility** — full Claude Code / Codex / OpenCode support across all skills, updated shim files, skill trigger disambiguation |
| 32 | **CLI Integration Tests** — 24 end-to-end CLI tests; informational output moved to stderr |
| 31 | **Bug Fixes & Hardening** — thread-safe logging bridge, correct zero-check scoring, connector MPN validation, SPICE value parser edge cases |

</details>

<details><summary>v0.22.0</summary>

| Sprint | Feature |
|-|-|
| 30 | **Confidence Dashboard** — `circuit-weaver confidence` aggregates 7 data sources into a 0-100 readiness score with HTML report; now a mandatory step in the wizard flow |
| 30 | **Workflow Overhaul** — wizard now 9 steps: added auto-detection, confidence check, and PCB layout preparation (placement optimizer, SVG editor, autoroute, DFM check) |
| 29 | **Enhanced Validations** — 3 new checks (power budget, thermal limits, signal integrity); cross-reference auditor validates spec-vs-schematic-vs-BOM consistency |
| 28 | **Circuit Simulation Engine** — SPICE netlist generation, ngspice runner with graceful degradation, simulation orchestrator with auto-planning and confidence scoring |
| 27 | **Project Discovery** — `circuit-weaver discover` auto-detects projects in CWD; all skills now pre-check before asking for paths |
| 26 | **Logging Overhaul** — 13 structured event types in `design.log`, Python logging bridge, `log-event` CLI for skill-callable logging, 7 modules instrumented |

</details>

<details><summary>v0.21.0</summary>

| Sprint | Feature |
|-|-|
| 25 | **Component Selection Rationale** — HTML review report now includes a per-IC table showing why each part was chosen, key electrical specs, and any reference design cited |
| 25 | **Auto Test Point Generation** — `generate_artifacts()` emits `{project}_test_points.csv` and test-point report data while leaving the validated schematic bytes unchanged (`annotated_schematic: false`); detects power, ground, clock, bus, and differential-pair nets |
| 24 | **Firmware Co-Design Export** — Auto-generates `{project}_pinout.csv`, STM32 `.ioc` skeleton, and ESP32 `sdkconfig.defaults` when MCU blocks are present |
| 23 | **KiCad CLI ERC Integration** — `circuit-weaver erc` runs KiCad's built-in ERC and surfaces results in the HTML report with a pass/fail badge |
| 22 | **Pinout Verification Gate** — ICs using unverified stub pinouts now fail validation before any schematic is emitted |

</details>

---

## Repo Layout

```
kicad_automations/
├── src/circuit_weaver/      # Core engine
│   ├── dispatcher.py           # Public API: validate, patch, generate, diff, pcb-feedback
│   ├── design_ir.py            # Canonical design intermediate representation (DesignIR)
│   ├── generator.py            # .kicad_sch file emitter
│   ├── validator.py            # 14-check validation pipeline (electrical + thermal + SI)
│   ├── cross_reference_validator.py  # Spec vs schematic vs BOM audit
│   ├── confidence_dashboard.py # Design readiness scoring (0–100) + HTML dashboard
│   ├── simulation.py           # Simulation orchestrator (plan → run → score)
│   ├── spice_netlist.py        # SPICE .cir netlist generator
│   ├── spice_runner.py         # ngspice subprocess runner with graceful degradation
│   ├── symbol_resolver.py      # IC symbol resolution chain (EasyEDA → cache → stub)
│   ├── symbol_cache.py         # Persistent symbol cache with full pin/power map schema
│   ├── research.py             # Research query orchestration (Perplexity / native web)
│   ├── research_store.py       # Research artifact persistence (JSON + summary.md)
│   ├── doctor.py               # Credential + backend diagnostics (circuit-weaver doctor)
│   ├── logging_bridge.py       # Unified logging: Python logging ↔ DesignLogger bridge
│   ├── design_logger.py        # Structured JSON Lines workflow logging (13 event types)
│   ├── project_discovery.py    # Auto-detect circuit projects in directories
│   ├── review_report.py        # HTML review report generator
│   ├── test_point_gen.py       # Auto test-point classification and CSV export
│   ├── firmware_export.py      # MCU co-design stubs (pinout CSV, .ioc, sdkconfig)
│   ├── placer.py               # Topology-aware schematic placement engine
│   ├── placement_optimizer.py  # Simulated annealing PCB placement optimizer
│   ├── placement_viewer.py     # Interactive HTML viewer (net highlight, thermal heatmap)
│   ├── svg_placement.py        # Bidirectional SVG placement editor (export + import)
│   ├── pcb_export.py           # Initial .kicad_pcb generation with zone-based layout
│   ├── design_scorer.py        # Electrical quality score (0–100, A–F)
│   ├── dfm_checker.py          # DFM rule checks
│   ├── thermal_analysis.py     # Thermal modeling and junction temp analysis
│   ├── si_constraints.py       # Signal integrity constraint solver
│   ├── api.py                  # FastAPI HTTP server
│   ├── helpers/placement.py    # KiCad API abstraction, footprint matching utilities
│   └── subcircuits/            # Reusable circuit template library (37 templates)
├── tests/                   # Regression test suite (1,200+ tests)
├── skills/                  # Global workflow skills: kicad, bom, digikey, lcsc, ee…
├── project-skills/          # Per-project templates: kicad-gen, autoroute, sim…
├── agents/                  # Hardware reviewer AI agent definitions
├── rules/                   # KiCad workflow policy files
├── samples/                 # Sample designs (iot_sensor_node, zigbee_humidistat…)
└── assets/                  # README visuals: banner, workflow diagram
```

---

## Agent Platform Support

| Platform | What's included |
|-|-|
| **Claude Code** | `/circuit-weaver` global skill via `install-skills` |
| **Codex** | `$circuit-weaver` from the current global `~/.agents/skills` location |
| **OpenCode** | Agent Skills from `~/.agents/skills`, or `$OPENCODE_CONFIG_DIR/skills` when configured |
| **Kilo** | Global skills under `$KILO_CONFIG_DIR/skills` or `~/.kilo/skills` |

Install for all platforms at once:

```bash
# Bash (Mac/Linux/WSL)
./install.sh --platform all

# PowerShell (Windows)
./install.ps1 -Platform all
```

The wrappers install the checkout and delegate skill copying, upgrades, dry runs, and conflict handling to the same Python installer. They honor `CLAUDE_CONFIG_DIR`, `OPENCODE_CONFIG_DIR`, and `KILO_CONFIG_DIR`; Codex uses `~/.agents/skills`. Use `--skills-only` / `-SkillsOnly` to avoid reinstalling the package.

---

## Sample Design

PyPI installs include a portable IoT starter. Copy it into a writable project
directory, then run the full workflow:

```bash
python -c "from importlib.resources import files; from pathlib import Path; d=Path('iot_sensor_example'); d.mkdir(exist_ok=True); d.joinpath('design.yaml').write_bytes(files('circuit_weaver').joinpath('examples','iot_sensor.yaml').read_bytes())"

# Validate
circuit-weaver validate iot_sensor_example/design.yaml

# Generate schematic + report + test points + firmware stubs
circuit-weaver generate iot_sensor_example/design.yaml -o ./output

# Export a BOM-only delivery (no heuristic CPL is invented)
circuit-weaver export-jlcpcb iot_sensor_example/design.yaml -o ./output/jlcpcb

# After creating a real electrical PCB, export a reconciled BOM + CPL
circuit-weaver export-jlcpcb iot_sensor_example/design.yaml \
    --pcb ./output/iot_sensor.kicad_pcb -o ./output/jlcpcb
```

A source checkout also includes the larger reference gallery under `samples/`.

---

## Contributing

```bash
# Install with dev dependencies
pip install -e ".[dev]"

# Install pre-commit hooks
pre-commit install

# Lint
python -m ruff check src tests

# Test
python -m pytest tests -q
```

Pre-commit hooks run ruff, YAML validation, and `circuit-weaver validate --strict` on changed design specs automatically.

---

## License

MIT. See [LICENSE](LICENSE).

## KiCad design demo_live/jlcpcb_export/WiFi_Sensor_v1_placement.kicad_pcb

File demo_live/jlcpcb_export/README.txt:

JLCPCB PCB Assembly Upload Instructions
==================================================

Project: WiFi_Sensor_v1

Files Included:
  - bom_jlcpcb.csv        BOM for parts matching
  - cpl_jlcpcb.csv        Centroid/placement file
  - (gerbers/)            Gerber files (export separately from KiCad)

Upload Steps:
  1. Go to https://jlcpcb.com/quote
  2. Upload Gerber ZIP file
  3. Configure PCB: 2-layer, 1.6mm thickness, color, quantity
  4. Proceed to quote
  5. Enable 'PCB Assembly'
  6. Upload BOM file (bom_jlcpcb.csv)
  7. Upload CPL file (cpl_jlcpcb.csv)
  8. Review part matching and confirm

Notes:
  - Parts with empty LCSC Part# must be sourced separately
  - JLCPCB basic parts (no setup fee): ~700 common components
  - Extended parts (setup fee $3 each): remaining components
  - Verify all part matches before confirming order

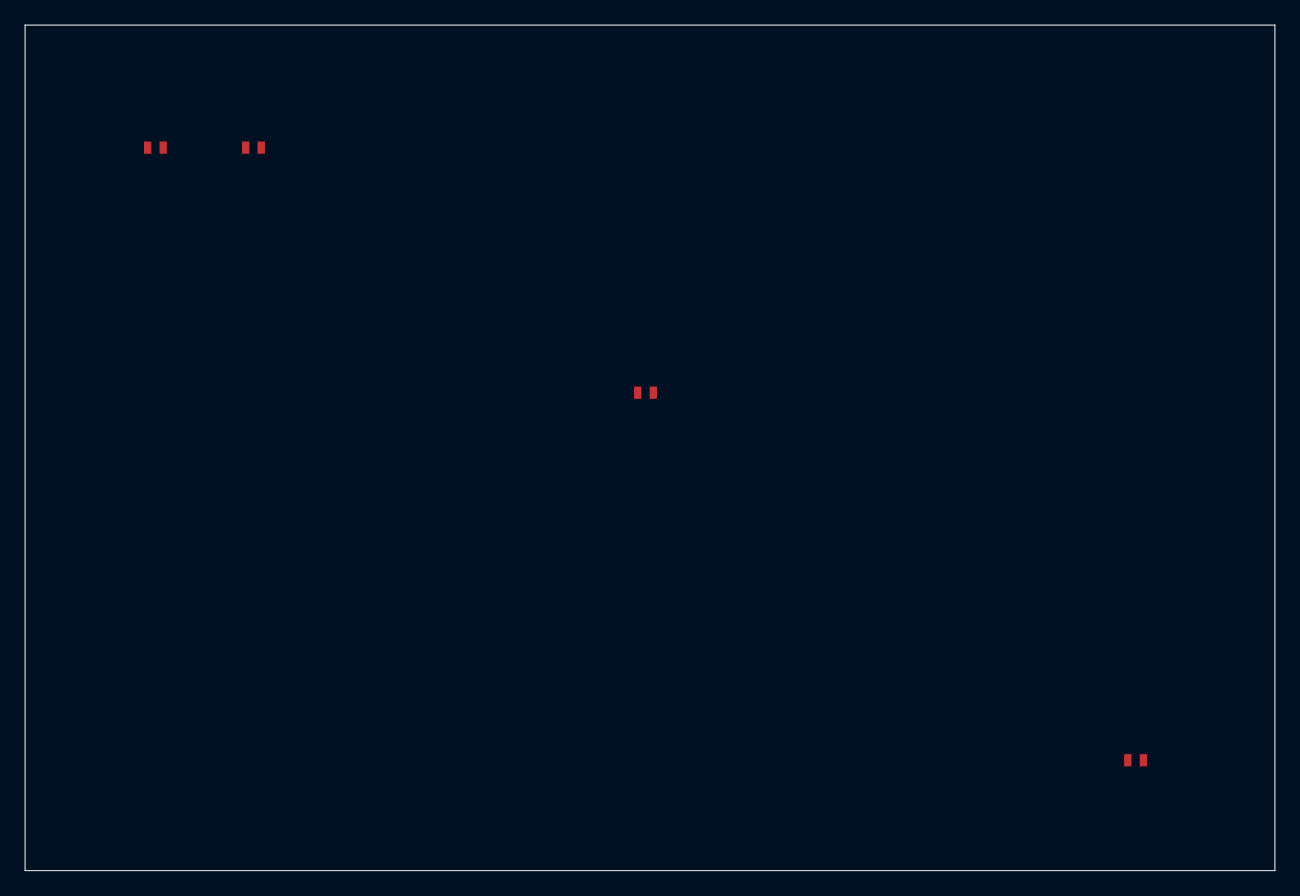
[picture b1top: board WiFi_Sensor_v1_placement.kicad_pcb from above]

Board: 2 copper layers, 102.0 x 69.0 mm, 4 parts (0 on the bottom side), 2 nets, no tracks yet.

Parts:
U1: TPS61230A; SOT-23-6
U2: AP62300; SOT-23-6
U3: ESP32-WROOM-32E
U4: BME280; Bosch_LGA-8_2.5x2.5mm

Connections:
GND: U1.2, U2.2, U3.1, U4.1
VDD_3P3: U3.2, U4.2

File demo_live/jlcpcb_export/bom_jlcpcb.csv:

Comment,Designator,Footprint,LCSC Part#
AP62300,U2,SOT-23-6,
BME280,U4,Bosch_LGA-8_2.5x2.5mm,
ESP32-WROOM-32E,U3,ESP32-WROOM-32E,
TPS61230A,U1,SOT-23-6,

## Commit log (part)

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2026-03-27 init: KiCad + EE automation skills for Claude Code
2026-04-02 new readme.md
2026-04-03 feat: Sprint 2 — template expansion & DFM quality (v0.3.0)
    New templates (6→10):
    - opamp: non-inverting/inverting/follower/differential with E24 feedback
    - protection: TVS diodes (SMBJ5.0A/12A, PESD5V0S1BA)
    - gate_driver: IR2110 (half-bridge+bootstrap), UCC27524 (dual low-side)
    - level_shifter: TXB0108 (8ch), TXS0102 (2ch)
    KiCad import improvements:
2026-04-03 feat: Sprint 5 Tasks 33-37 — EasyEDA/LCSC symbol import pipeline (v0.6.0)
    Add 4th-tier component resolution via EasyEDA's public API (no auth).
    When a part isn't in the built-in registry or KiCad official library,
    fetch its symbol from EasyEDA by LCSC part number (300K+ parts).
    - easyeda_api.py: stdlib HTTP client with 7-day disk cache
    - easyeda_parser.py: tilde-delimited shape → ComponentDef converter
    - project_spec.py: integrated as fallback before stub creation
2026-04-05 feat: Sprint 2 — power domain integrity, pin inference, PWR_FLAG, cross-checks
    S2.1: Fix template power pin issues:
    - opamp.py: replace hardcoded pin numbers with database lookups (pin_out_a,
    pin_inm_a, pin_inp_a fields added to all 3 IC entries)
    - power_mux.py: replace hardcoded LTC4357 VIN pins 6/7/8 with pin_vin_extra
    database field and iteration loop
    - can_transceiver.py: move RS pin from power_pins to pin_nets (RS is input
2026-04-05 feat: Sprint 9 — unblock day-1 onboarding (v0.8.0)
    S9.1: Fix example designs and bootstrap tests
    - Fix net connectivity validator to count bypass_caps/straps as connections
    (SW/FB/BST pins on buck converters no longer flagged as dangling)
    - Summarize MCU floating GPIOs into one warning instead of 28 individual
    - Fix bootstrap tests to tolerate KiCad CLI unavailability (2 tests fixed)
    S9.2: Add list-templates CLI command
2026-04-05 feat: automated demo video recording with selenium + mss + opencv
2026-04-06 docs: add live CLI demo with interactive web player
    Creates a complete, production-ready demo package:
    - index.html: Interactive asciinema web player (self-contained, 14 KB)
    - demo.cast: Terminal recording showing 6-step design workflow (5.6 KB)
    - DEMO_WALKTHROUGH.md: Detailed step-by-step walkthrough with all outputs
    - WEBSITE_INTEGRATION.md: How to deploy demo to website (GitHub Pages, static hosts, etc.)
    - Real generated artifacts: WiFi sensor schematic, BOM, CPL files
2026-04-06 docs: Clean up demo README — proper HTML5 video embed, table layout, simplified navigation
2026-04-06 feat: Ultra-readable demo GIF — mobile-friendly, huge fonts, visible CLI commands
    demo_ultra_readable.gif (399 KB, 28 seconds):
    - 1400ms per frame (2.8x slower than professional version)
    - 32pt title fonts, 18pt descriptions — readable on mobile
    - Yellow command boxes showing exact CLI prompts:
    * circuit-weaver list-templates
    * circuit-weaver scaffold
2026-04-06 docs: Update CHANGELOG for /circuit-weaver skill implementation (v0.10.1)
2026-04-06 feat: Project folder management for circuit design workflow
    FOLDER STRUCTURE:
    - New circuits are created in named folders (root_dir/<project_name>/)
    - design.yaml and design.log are saved in the project folder
    - No more dumping files into current directory root
    WORKFLOW CHANGES:
    - design-wizard now routes to new vs existing circuit workflow
2026-04-06 docs: Fix design_wizard/SKILL.md — remove unimplemented promises, add output formatting rules (Task 70)
    Changes:
    - Added 'Output Formatting Rules' section showing expected CLI output for each command
    - Updated Step 6a PCB Kickoff to be realistic: removed unimplemented promises (Python scripts, fiducial markers)
    - Emphasized manual KiCad work (placement, routing, silkscreen) as the primary path
    - Positioned autorouting (Freerouting) as optional add-on, not core workflow
    - Verified scaffold + apply-patch commands are correct
2026-04-06 fix: Preparser: recognize 'blocks' list as native engine format
    Add 'blocks' key to recognized block types in _has_blocks(). The generic blocks list format is a valid engine spec format used in tests and some specs.
    This allows specs like {"project": "test", "blocks": [...]} to be recognized as already in engine format, fixing presentation profile tests.
2026-04-06 fix: Ruff linting errors - missing imports, long lines, import order
    - mvp.py: Add missing 'time' import
    - preparser.py: Remove unused 'blocks' variable
    - generator.py: Move imports to top of file (E402)
    - diff_renderer.py: Break long HTML strings to fit 120 char limit
    - mvp.py: Extract long command strings to variables
    - validator.py: Break long suggestion string
2026-04-07 plan: Add Tasks 93–96 for SVG placement editor and spec harvesting
    Task 93 — SVG Placement Editor (P1, MEDIUM):
    - Bidirectional SVG ↔ placement format conversion
    - Users edit in Inkscape/CorelDRAW (free tools they know)
    - No custom web UI needed; git-friendly for design review
    - Workflow: export → edit → import-placement
    Task 94 — Unified Datasheet Harvester (P1, LARGE):
2026-04-07 feat: Task 86 — auto-source dispatch + spec update (v0.12.0)
    Task 86 (MEDIUM): Auto-populate BOM during generation
    - Added --auto-source and --update-spec flags to generate subcommand
    - Implemented _auto_source_report() helper function:
    * Iterates through components and queries PartsLookup, DigiKey, Mouser
    * Returns summary dict with resolved count, by_source breakdown, unresolved list
    - Implemented update_spec_with_sourced_data() in project_spec.py:
2026-04-07 fix: Sprint 14 hardening — SVG transform parsing, logging, and docs (v0.12.0)
    Task 93 (SVG placement): Enhanced _parse_transform() to handle GIMP/Inkscape variants
    - Supports translate(x, y), translate(x y), translate(x), and implicit y=0
    - Handles rotate(angle) and rotate(angle cx cy) — extracts angle only
    - Fallback to matrix(a b c d e f) parsing for affine transforms
    - Graceful error handling with logging for parse failures
    - Wrapped import_placement_from_svg calls in try/except for robustness
2026-04-07 docs: Sprint 18 — OpenSCAD enclosure designer + KiCad API integration
    Document two new post-Sprint-17 enhancements in v0.14.1:
    1. OpenSCAD Enclosure Designer (Task 102)
    - Parametric 3D-printable enclosure generation
    - Customizable walls, ports, mounting holes, vents
    - design-enclosure CLI subcommand
    2. KiCad Python API Integration (Task 103)
2026-04-07 fix: Clean up unused imports and variables in linting
    - kicad_placement_api.py: Use importlib.util.find_spec for pcbnew availability check (F821, F401)
    - mvp.py: Use empty list for optimize_placement (undefined compiled variable), prefix unused svg_str (F821, F841)
    - placement_viewer.py: Remove unused value variable assignment (F841)
    All ruff checks now pass.
2026-04-07 fix: Add missing os import in test_import_pipeline.py
2026-04-07 feat: Add log-view command and enhance project logging visibility
    New feature: 'log-view' CLI command to inspect design workflow logs
    - View recent log entries (JSON Lines format)
    - Filter by entry type (wizard_step, cli_call, validation, research)
    - Show last N entries with human-readable timestamps
    - Helps troubleshoot design issues and resume incomplete projects
    Enhanced wizard output:
2026-04-07 fix: Restructure design wizard for proper skill-based interactive prompts
    Fixes UX regression where interactive prompts weren't working in Claude Code.
    Architecture change: Move all interactive UI logic from Python code to SKILL.md
    instructions. Python can't invoke Claude Code tools (AskUserQuestion) — only Claude
    itself can. Solution maintains cross-platform support:
    Changes:
    - Delete src/circuit_weaver/interactive_prompts.py (dead code)
2026-04-07 feat: Design DFM checker and design documentation generator (Tasks 104 + 108)
    - dfm_checker.py: Validate PCB designs against fab capabilities (trace width, spacing, via size, annular ring, clearance)
    - design_docs.py: Auto-generate assembly guides, power budgets, ordering checklists, datasheet indexes
    - Added 31 tests covering DFM violations, design doc generation, CSV/markdown exports
    - Integrated check-dfm and generate-docs CLI subcommands into mvp.py dispatcher
    - All tests passing: 31/31 ✓
    Tasks:
2026-04-07 fix: Update test CLI module references to dispatcher (Task 109)
2026-04-08 fix: Update test assertion to match shortened warning indicator
2026-04-08 feat: Sprint 22 Tasks 116-117 — pinout verification gate (v0.18.0)
    Task 116: Add _validate_pinout_sources() to validator.py.
    Emits error-level unverified-pinout issue for any IC with
    pinout_source="stub" unless pinout_verified=True is set.
    Registered as first check in _VALIDATION_CHECKS.
    Task 117: Replace STUB annotation strings in digikey_loader.py and
    mouser_loader.py with pinout_source="stub" field on ComponentDef.
2026-04-09 docs: add PCB placement workflow section to README
    - PCB Placement Workflow section covering all 6 steps:
    optimize-placement (SA optimizer), placement-viewer (interactive HTML),
    SVG round-trip editing, KiCad API write-back, DFM check, panelization
    - Expanded CLI Reference with placement, BOM, and design-tools groups
    - Repo layout updated with placer.py, placement_optimizer.py,
    placement_viewer.py, svg_placement.py, kicad_placement_api.py,
2026-04-10 docs: update changelog, tasks, readme, workflow, CLI ref, and architecture
    - CHANGELOG.md: Add v0.22.0 with Sprints 26-30 (logging, discovery,
    simulation, validations, confidence dashboard)
    - TASKS.md: Add Sprint 26-30 task entries (Tasks 125-130), all marked DONE
    - README.md: Add simulate/confidence/discover/log-event to CLI reference,
    update What's New to v0.22.0, update Repo Layout with 7 new modules,
    collapse v0.21.0 into details block
2026-04-22 fix: Sprint 31 — bug fixes and error handling hardening (v0.23.0)
    Task 131: Fix _score_from_issues() returning 100 when total_checks=0
    but errors > 0. Now correctly penalizes errors even with 0 checks.
    Task 132: Add threading.Lock to logging bridge for thread-safe access
    to _current_logger and _file_handler. Wrap cleanup_logging() in
    try/finally so set_design_logger(None) always runs even on error.
    Task 133: Remove connectors ("J") from passive prefixes in cross-ref
2026-04-22 feat: Sprint 34 — data-driven template engine + 7 new templates (v0.24.0)
    Replace hardcoded subcircuit template classes with a JSON-driven IC data
    system and dynamic topology builders. Expand template library from 30 to 37.
    New ic_data/ package with 11 JSON files (amplifier, bus_interface, connector,
    converter, custom, linear_regulator, memory, misc, oscillator, protection,
    switching_regulator) storing pin maps, topology classifiers, and electrical
    parameters.
2026-04-22 fix: Sprint 36 Tasks 151-155 — resolver chain fix (v0.25.0)
    Users reported v0.24.x stubbed common parts (SHT41-AD1B-R2, SGP40-D-R4,
    nRF52840) even though DigiKey, Mouser, and ic_data JSON all carried
    them. Root cause: project_spec._resolve_component() had its own ad-hoc
    3-tier inline resolver (registry → KiCad lib → EasyEDA) that never
    delegated to SymbolResolver's richer chain, and ic_data was never a
    resolver tier at all — it was a side-store used only by the template
2026-04-23 chore: regenerate 8 sample designs against v0.27.0 engine
    All 8 samples pass full validation (0 ERC errors):
    - led_power_indicator, iot_sensor_node, usb_regulated_supply,
    usb_uart_bridge, oled_display_module, battery_iot_sensor,
    motor_controller, fpga_power_carrier
    New artifacts per sample: .kicad_sch, _test_points.csv, _pinout.csv,
    canonical_spec.yaml, design_ir.json, validation_report.json; MCU samples
2026-04-24 chore: add kilo.json, update agent configs, expand .gitignore
    - Add kilo.json (Kilo AI project config for bom-auditor/hardware-reviewer agents)
    - Expand .gitignore with tool cache dirs (.kilo/, .mypy_cache/, .code-review-graph/, .wt-*/, memory/)
    - Update AGENTS.md, agents/, .opencode/agents/, docs/agent-platforms.md, install scripts, opencode.json
    - Delete ffmpeg.exe (223 MB), demo_humidistat.cast, and stale .wt-b02cbbc/ worktree dir
2026-04-26 fix: include ic_data/*.json in wheel package-data (broken in 0.28.1)
2026-04-28 docs: add cache-friendly agent workflow guidelines
    DeepSeek bills cache-miss tokens at ~120x cache-hit cost. OpenCode's non-deterministic sub-agent prompt construction breaks prefix-based caching. Codify what we control: reuse task sessions, avoid su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
2026-04-29 fix: add httpx to api extras for fastapi TestClient
2026-05-01 feat: complete Sprint 49 legacy migration (v0.30.4)
